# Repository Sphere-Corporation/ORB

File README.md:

<!-- PROJECT LOGO -->
<br />

  <p align="center">
    An Intel 1702A Emulator for the Sphere-1 CPU/2 Board
      </p>
<p align="center">
    <strong>
    "Optional ROM Board"
    </strong>
</p>
</div>

<!-- ABOUT THE PROJECT -->
## About The Project

Whilst building the reproduction CPU/2, I found (not a surprise) that some of the parts are becoming increasingly rare and expensive to find. One clear example of this is the Intel 1702A EPROMs.

These chips are integral to the CPU/2 board, as they contain the “Operating System” for the whole computer.

Project ORB, then, is a project to allow these chips to be simulated, and therefore not require expensive replacement chips.

## Contributing

Contributions are what make the open source community such an amazing place to learn, inspire, and create. Any contributions you make are **greatly appreciated**.

If you have a suggestion or a resource that would help me, or perhaps you see something I've got wrong, please create an Issue. 

<!-- LICENSE 
## License

Distributed under the MIT License. See `LICENSE.txt` for more information.
-->

<!-- CONTACT -->
## Contact

eMail [Andrew Shapton](mailto:alshapton@gmail.com)

<!-- ACKNOWLEDGMENTS -->
## Acknowledgments

I have to give my heartfelt thanks to Ben Zotto, who has been a sounding board for me throughout this project, answering my emails, and checking his Sphere-1 CPU/2 board to answer questions, and offering thoughts as to why things “were like they were” ! Without him, I would never have got as far as I have.

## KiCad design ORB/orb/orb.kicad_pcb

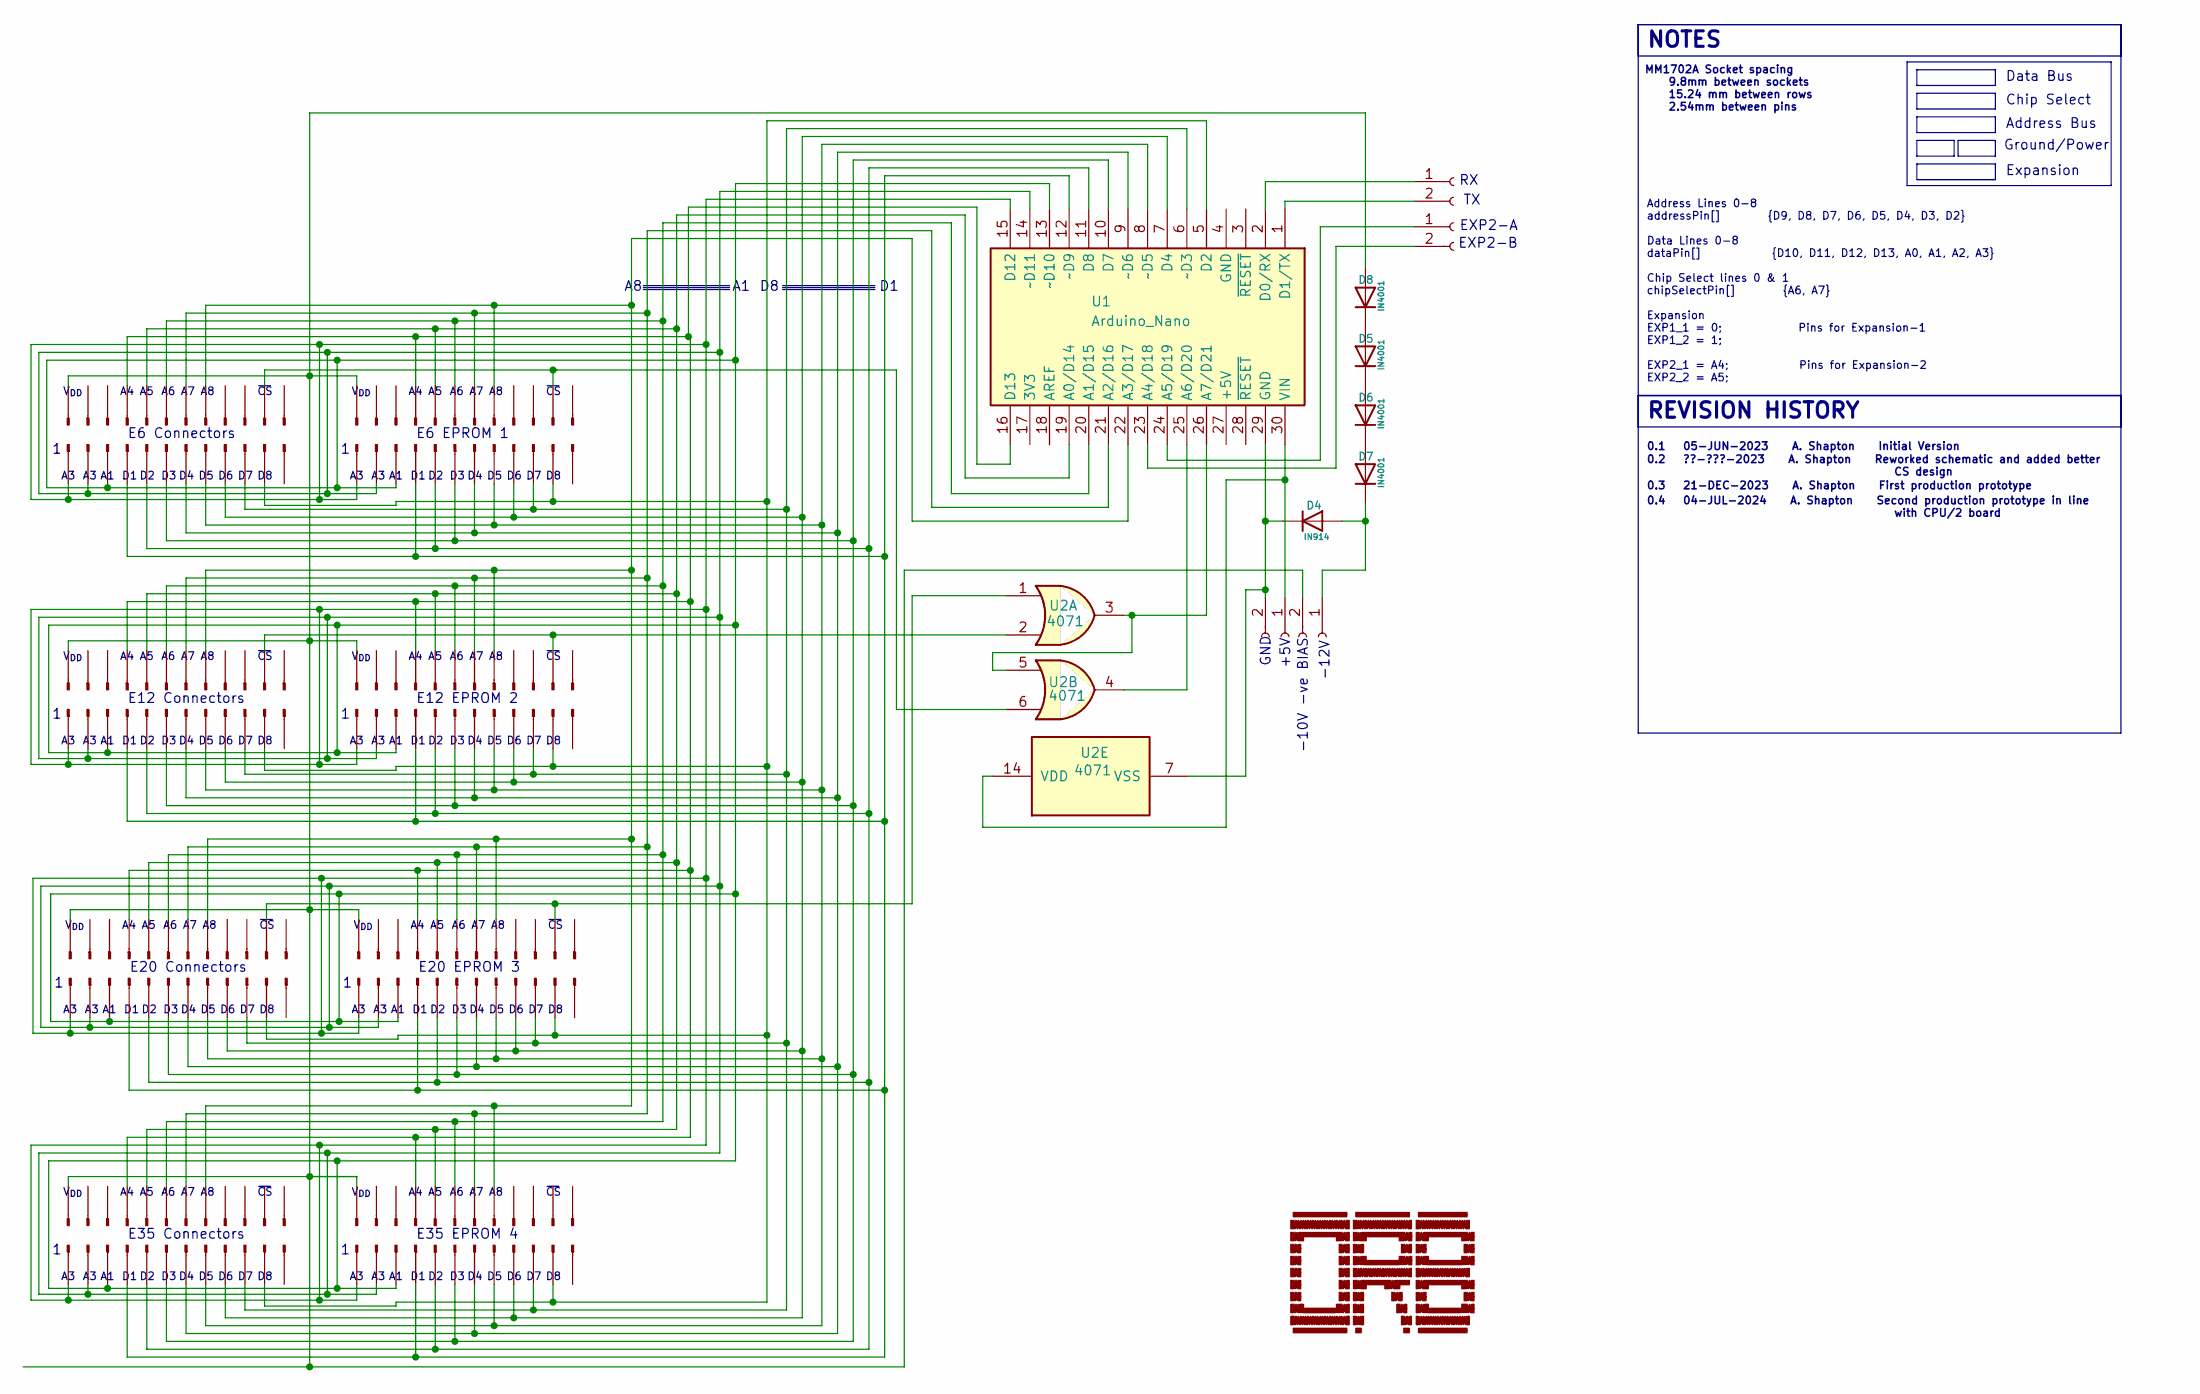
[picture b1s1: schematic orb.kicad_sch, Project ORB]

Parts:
D4: IN914; D_DO-41_SOD81_P10.16mm_Horizontal
D5, D6, D7, D8: IN4001; D_DO-41_SOD81_P10.16mm_Horizontal
E6-1, E6-3: E6-1C; PinHeader_1x12_P2.54mm_Vertical
E6-2, E6-4, E12-1, E12-2, E12-3, E12-4, E20-1, E20-2, E20-3, E20-4, E35-1, E35-2, E35-3, E35-4: Conn_01x12_Pin; PinHeader_1x12_P2.54mm_Vertical
J1, J2, J3, J4: Conn_01x02_Socket; PinSocket_1x02_P2.54mm_Vertical
U1: Arduino_Nano
U2: 4071; DIP-14_W7.62mm_Socket_LongPads

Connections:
unnamed: D4.2 (A), D7.1 (K), J4.1
unnamed: D4.1 (K), J1.2, U1.29 (GND), U2.7 (VSS)
unnamed: D5.2 (A), D8.1 (K)
unnamed: D5.1 (K), D6.2 (A)
unnamed: D6.1 (K), D7.2 (A)
unnamed: D8.2 (A), E6-1.1, E6-3.1, E12-1.1, E12-3.1, E20-1.1, E20-3.1, E35-1.1, E35-3.1, J4.2
unnamed: E6-1.11, E6-3.11, U2.6
unnamed: E6-1.4, E6-3.4, E12-1.4, E12-3.4, E20-1.4, E20-3.4, E35-1.4, E35-3.4, U1.16 (D13)
unnamed: E6-1.5, E6-3.5, E12-1.5, E12-3.5, E20-1.5, E20-3.5, E35-1.5, E35-3.5, U1.19 (A0/D14)
unnamed: E6-1.6, E6-3.6, E12-1.6, E12-3.6, E20-1.6, E20-3.6, E35-1.6, E35-3.6, U1.20 (A1/D15)
unnamed: E6-1.7, E6-3.7, E12-1.7, E12-3.7, E20-1.7, E20-3.7, E35-1.7, E35-3.7, U1.21 (A2/D16)
unnamed: E6-1.8, E6-3.8, E12-1.8, E12-3.8, E20-1.8, E20-3.8, E35-1.8, E35-3.8, U1.22 (A3/D17)
unnamed: E12-1.11, E12-3.11, U2.2
unnamed: E6-2.2, E6-4.2, E12-2.2, E12-4.2, E20-2.2, E20-4.2, E35-2.2, E35-4.2, U1.5 (D2)
unnamed: E6-2.3, E6-4.3, E12-2.3, E12-4.3, E20-2.3, E20-4.3, E35-2.3, E35-4.3, U1.6 (~D3)
unnamed: E6-2.4, E6-4.4, E12-2.4, E12-4.4, E20-2.4, E20-4.4, E35-2.4, E35-4.4, U1.7 (D4)
unnamed: E6-2.5, E6-4.5, E12-2.5, E12-4.5, E20-2.5, E20-4.5, E35-2.5, E35-4.5, U1.8 (~D5)
unnamed: E6-2.6, E6-4.6, E12-2.6, E12-4.6, E20-2.6, E20-4.6, E35-2.6, E35-4.6, U1.9 (~D6)
unnamed: E6-2.7, E6-4.7, E12-2.7, E12-4.7, E20-2.7, E20-4.7, E35-2.7, E35-4.7, U1.10 (D7)
unnamed: E6-2.8, E6-4.8, E12-2.8, E12-4.8, E20-2.8, E20-4.8, E35-2.8, E35-4.8, U1.11 (D8)
unnamed: E6-2.9, E6-4.9, E12-2.9, E12-4.9, E20-2.9, E20-4.9, E35-2.9, E35-4.9, U1.12 (~D9)
unnamed: E6-2.10, E6-4.10, E12-2.10, E12-4.10, E20-2.10, E20-4.10, E35-2.10, E35-4.10, U1.13 (~D10)
unnamed: E6-2.11, E6-4.11, E12-2.11, E12-4.11, E20-2.11, E20-4.11, E35-2.11, E35-4.11, U1.14 (~D11)
unnamed: E6-2.12, E6-4.12, E12-2.12, E12-4.12, E20-2.12, E20-4.12, E35-2.12, E35-4.12, U1.15 (D12)
unnamed: E20-1.11, E20-3.11, U2.1
unnamed: J1.1, U1.30 (VIN), U2.14 (VDD)
unnamed: J2.1, U1.2 (D0/RX)
unnamed: J2.2, U1.1 (D1/TX)
unnamed: J3.1, U1.24 (A5/D19)
unnamed: J3.2, U1.23 (A4/D18)
unnamed: U1.25 (A6/D20), U2.4
unnamed: U1.26 (A7/D21), U2.3, U2.5

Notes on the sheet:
V_{DD}
-12V
E20 EPROM 3
E6 Connectors
-10V -ve BIAS
Data Bus
E20 Connectors
EXP2-A
0.4 04-JUL-2024 A. Shapton Second production prototype in line with CPU/2 board
E35 Connectors
EXP2-B
Expansion
GND
NOTES
E12 EPROM 2
0.2 ??-???-2023 A. Shapton Reworked schematic and added better CS design
Address Bus
0.3 21-DEC-2023 A. Shapton First production prototype
Ground/Power
REVISION HISTORY
Address Lines 0-8 addressPin[] {D9, D8, D7, D6, D5, D4, D3, D2} Data Lines 0-8 dataPin[] {D10, D11, D12, D13, A0, A1, A2, A3} Chip Select lines 0 & 1 chipSelectPin[] {A6, A7} Expansion EXP1_1 = 0; Pins for Expansion-1 EXP1_2 = 1; EXP2_1 = A4; Pins for Expansion-2 EXP2_2 = A5;
E35 EPROM 4
E6 EPROM 1
0.1 05-JUN-2023 A. Shapton Initial Version
Chip Select
MM1702A Socket spacing 9.8mm between sockets 15.24 mm between rows 2.54mm between pins
E12 Connectors
+5V

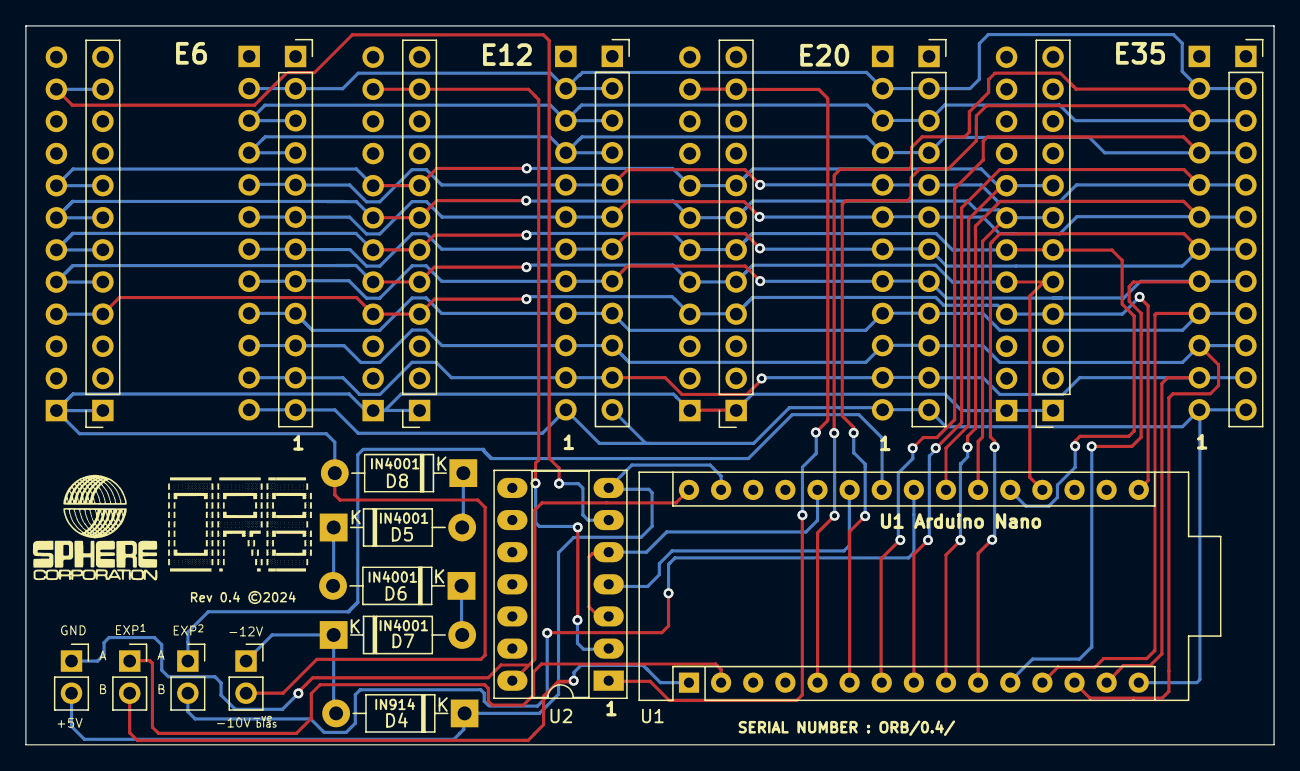
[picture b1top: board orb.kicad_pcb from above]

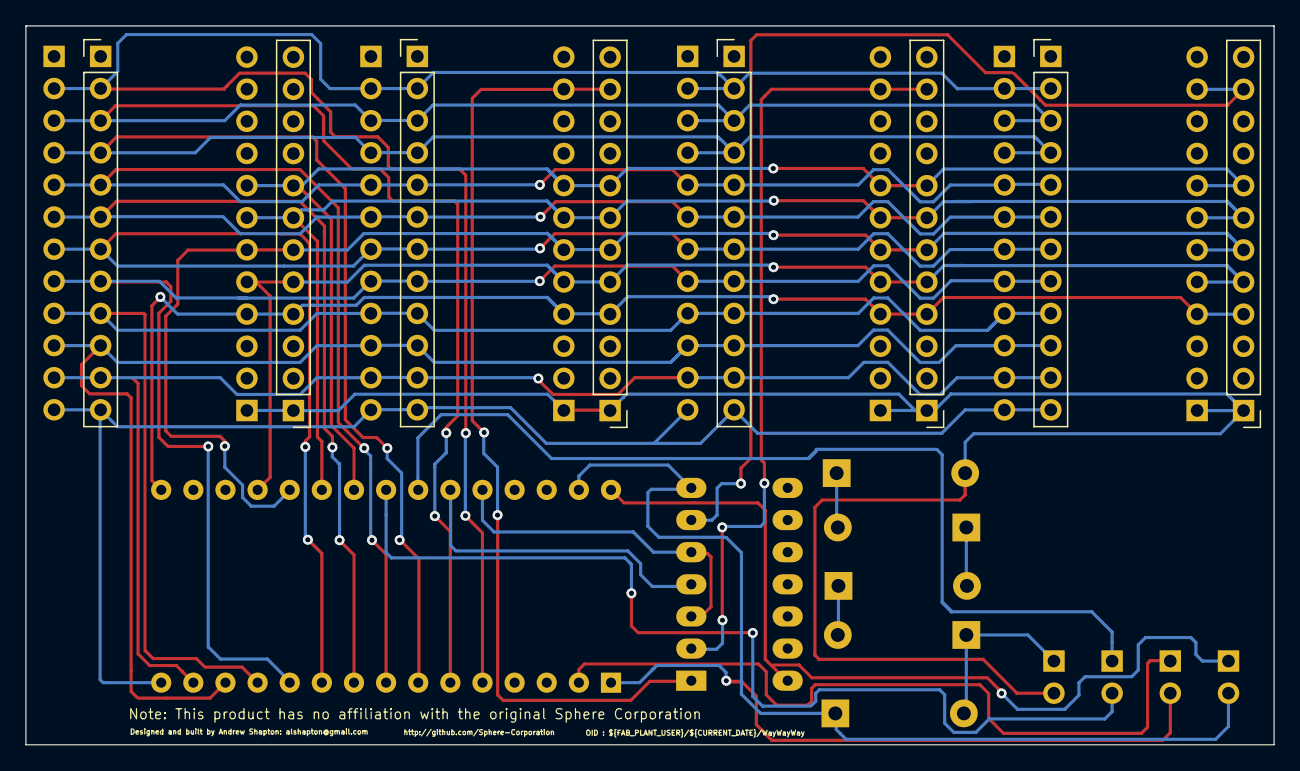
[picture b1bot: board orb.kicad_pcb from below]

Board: 2 copper layers, 98.7 x 56.8 mm, 27 parts (8 on the bottom side), 32 nets.

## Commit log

2023-08-22 update commit to complete repo upload
2023-08-24 Added README to the submodule
2023-12-24 Final conversion of convertROM script to Python
2023-12-24 Tidied up directories ready to ship tool out to CONVERT tool library
2024-04-02 Final commit before disassociating repos
2024-04-02 Last commit - tidying up
2024-07-16 Updated for 0.4.alpha release
2024-07-16 Removed erroneous .zip file
2024-07-16 Rebased
2024-12-28 Initial recommit
2024-12-28 Added .gitignore
2025-10-08 Added facility to select ROMs when compiling, also added test ROM

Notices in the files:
ORB/orb/orb.kicad_pcb:
Rev 0.4 ©2024
